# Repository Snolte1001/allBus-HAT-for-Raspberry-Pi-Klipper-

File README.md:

# allBus-HAT-for-Raspberry-Pi
I developed the expansion board to make all buses of the Raspberry Pi which are useful for the operation with Klipper easily accessible, to avoid wiring errors and to keep the construction as compact as possible.

Another requirement was to design the power management so that a proper startup and shutdown is possible, in addition there should be no standby power.  

## This HAT has no dependencies to Klipper, it can also be used for any other application without restrictions.

## **Power Funtions:**  
The HAT is supplied with 5V via screw terminals and can handle 3A current.  
a push button and an LED can be connected to the HAT on the port provided for this purpose.  
  
The button triggers a Mosfet circuit that supplies the Pi with power, the LED lights up as soon as the Pi starts.  
If the button is pressed again the LED starts blinking for 3 seconds, if pressed again during this time the Pi will initiate a proper shutdown and then reset the Mosfet, the Pi is now completely powerless.  
A long press of the button leads to a hard disconnect of the power supply.  

In addition, two GPIO(22,27) are led out which can be used, for example, to control a relay for the main power supply of a 3D printer (Attention: this would require a downstream circuit that switches the load with a transistor). 

For this Power ON/OFF function only one GPIO(4) is needed and does not limit the availability of the I2C bus because none of these pins is needed.  
Another GPIO(17) is used for the status LED. 

With a jumper you can choose if the Pi should boot automatically after applying the 5V power supply or if it should stay off.  

The basic idea of the ON/OFF circuit comes from this page:  
http://www.mosaic-industries.com/embedded-systems/microcontroller-projects/raspberry-pi/on-off-power-controller

## **Bus Features:**  
-CAN Bus on SPI0 (e.g. to connect the Pi internally with the MCU)   
-UART (e.g. to connect the Pi internally with the MCU)  
-SPI1 (e.g. for input shaper. Note: it still needs to be tested)  
-I2C (e.g. for input shaper)  

## **Installation:**  
1. preparation in boot/config.txt  
  coming soon
2. installation of the shutdown script  
  coming soon
  
## **Note for Klipper/MainsailOS/Fluidd users:**  
do not try to control the power control line (GPIO4) by software yourself ! This is blocked by the dtoverlay=gpio-poweroff, so it is also prevented that unintentionally a hard shutdown is triggered !

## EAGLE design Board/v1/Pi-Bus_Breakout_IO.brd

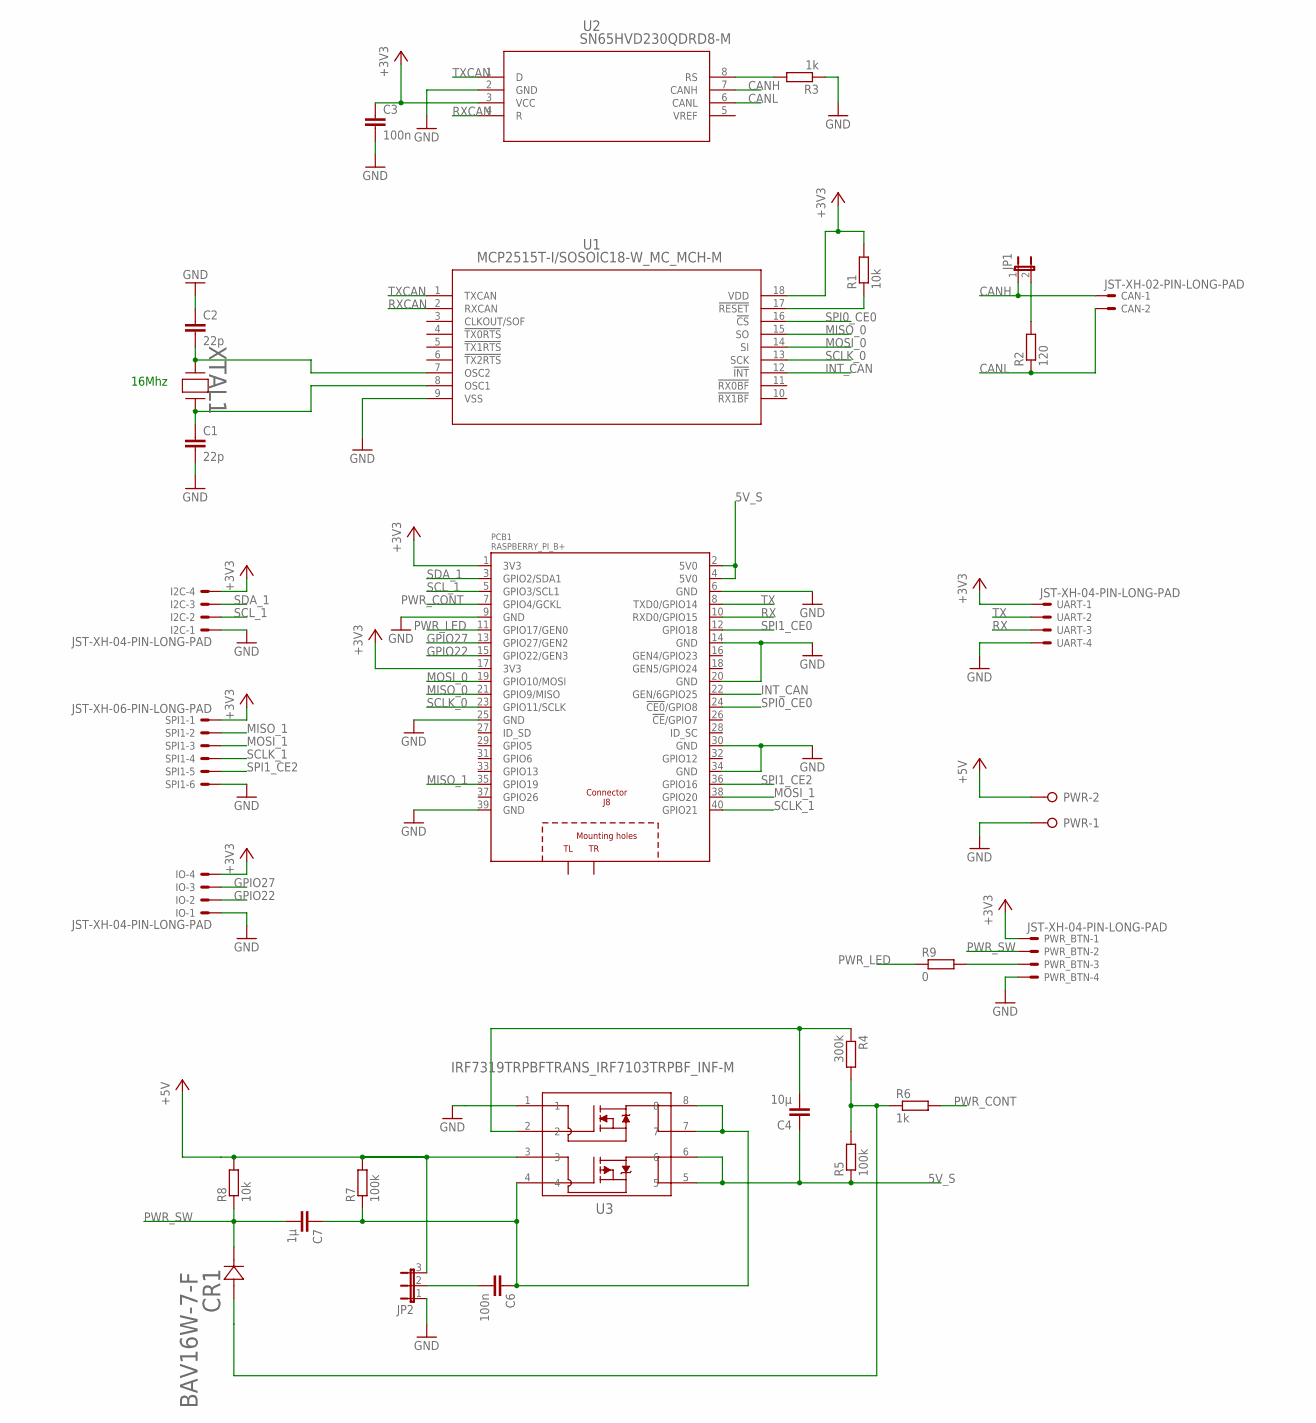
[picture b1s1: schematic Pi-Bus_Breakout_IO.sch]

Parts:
C1, C2: 22p; C0805
C3, C6: 100n; C0805
C4: 10µ; C0805
C7: 1µ; C0805
CAN: JST-XH-02-PIN-LONG-PAD; JST-XH-02-PACKAGE-LONG-PAD
CR1: BAV16W-7-F; SOD123_DIO
I2C: JST-XH-04-PIN-LONG-PAD; JST-XH-04-PACKAGE-LONG-PAD
IO: JST-XH-04-PIN-LONG-PAD; JST-XH-04-PACKAGE-LONG-PAD
JP1: JP1E; JP1
JP2: JP2E; JP2
PCB1: RASPBERRY_PI_B+
PWR: W237-02P; W237-132
PWR_BTN: JST-XH-04-PIN-LONG-PAD; JST-XH-04-PACKAGE-LONG-PAD
R1, R8: 10k; R0805
R2: 120; R0805
R3, R6: 1k; R0805
R4: 300k; R0805
R5, R7: 100k; R0805
R9: 0; R0805
SPI1: JST-XH-06-PIN-LONG-PAD; JST-XH-06-PACKAGE-LONG-PAD
U1: MCP2515T-I/SOSOIC18-W_MC_MCH-M; SOIC18-W_MC_MCH-M
U2: SN65HVD230QDRD8-M; D8-M
U3: IRF7319TRPBFTRANS_IRF7103TRPBF_INF-M; TRANS_IRF7103TRPBF_INF-M
UART: JST-XH-04-PIN-LONG-PAD; JST-XH-04-PACKAGE-LONG-PAD
XTAL1: 8Mhz; XTAL_8PF/ATF_EUR

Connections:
5V_S: C4.1, PCB1.2 (5V0), PCB1.4 (5V0), R5.1, U3.5, U3.6
+3V3: C3.1, I2C.4, IO.4, PCB1.1 (3V3), PCB1.17 (3V3), PWR_BTN.1, R1.2, SPI1.1, U1.18 (VDD), U2.3 (VCC), UART.1
+5V: JP2.3, PWR.2, R7.2, R8.2, U3.3
CANH: CAN.1, JP1.1, U2.7 (CANH)
CANL: CAN.2, R2.1, U2.6 (CANL)
GND: C1.2, C2.1, C3.2, I2C.1, IO.1, JP2.1, PCB1.6 (GND), PCB1.9 (GND), PCB1.14 (GND), PCB1.20 (GND), PCB1.25 (GND), PCB1.30 (GND), PCB1.34 (GND), PCB1.39 (GND), PWR.1, PWR_BTN.4, R3.1, SPI1.6, U1.9 (VSS), U2.2 (GND), U3.1, UART.4
GPIO22: IO.2, PCB1.15 (GPIO22/GEN3)
GPIO27: IO.3, PCB1.13 (GPIO27/GEN2)
INT_CAN: PCB1.22 (GEN/6GPIO25), U1.12 (!INT)
MISO_0: PCB1.21 (GPIO9/MISO), U1.15 (SO)
MISO_1: PCB1.35 (GPIO19), SPI1.2
MOSI_0: PCB1.19 (GPIO10/MOSI), U1.14 (SI)
MOSI_1: PCB1.38 (GPIO20), SPI1.3
unnamed: R1.1, U1.17 (!RESET)
unnamed: C1.1, U1.8 (OSC1), XTAL1.2
unnamed: C2.2, U1.7 (OSC2), XTAL1.1
unnamed: R3.2, U2.8 (RS)
unnamed: JP1.2, R2.2
unnamed: CR1.2, R4.2, R5.2, R6.1
unnamed: PWR_BTN.3, R9.2
unnamed: C4.2, R4.1, U3.2
unnamed: C6.2, JP2.2
unnamed: C6.1, C7.1, R7.1, U3.4, U3.7, U3.8
PWR_CONT: PCB1.7 (GPIO4/GCKL), R6.2
PWR_LED: PCB1.11 (GPIO17/GEN0), R9.1
PWR_SW: C7.2, CR1.1, PWR_BTN.2, R8.1
RX: PCB1.10 (RXD0/GPIO15), UART.3
RXCAN: U1.2 (RXCAN), U2.4 (R)
SCLK_0: PCB1.23 (GPIO11/SCLK), U1.13 (SCK)
SCLK_1: PCB1.40 (GPIO21), SPI1.4
SCL_1: I2C.2, PCB1.5 (GPIO3/SCL1)
SDA_1: I2C.3, PCB1.3 (GPIO2/SDA1)
SPI0_CE0: PCB1.24 (!CE0!/GPIO8), U1.16 (!CS)
SPI1_CE0: PCB1.12 (GPIO18)
SPI1_CE2: PCB1.36 (GPIO16), SPI1.5
TX: PCB1.8 (TXD0/GPIO14), UART.2
TXCAN: U1.1 (TXCAN), U2.1 (D)
VREF: U2.5 (VREF)

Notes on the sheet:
16Mhz

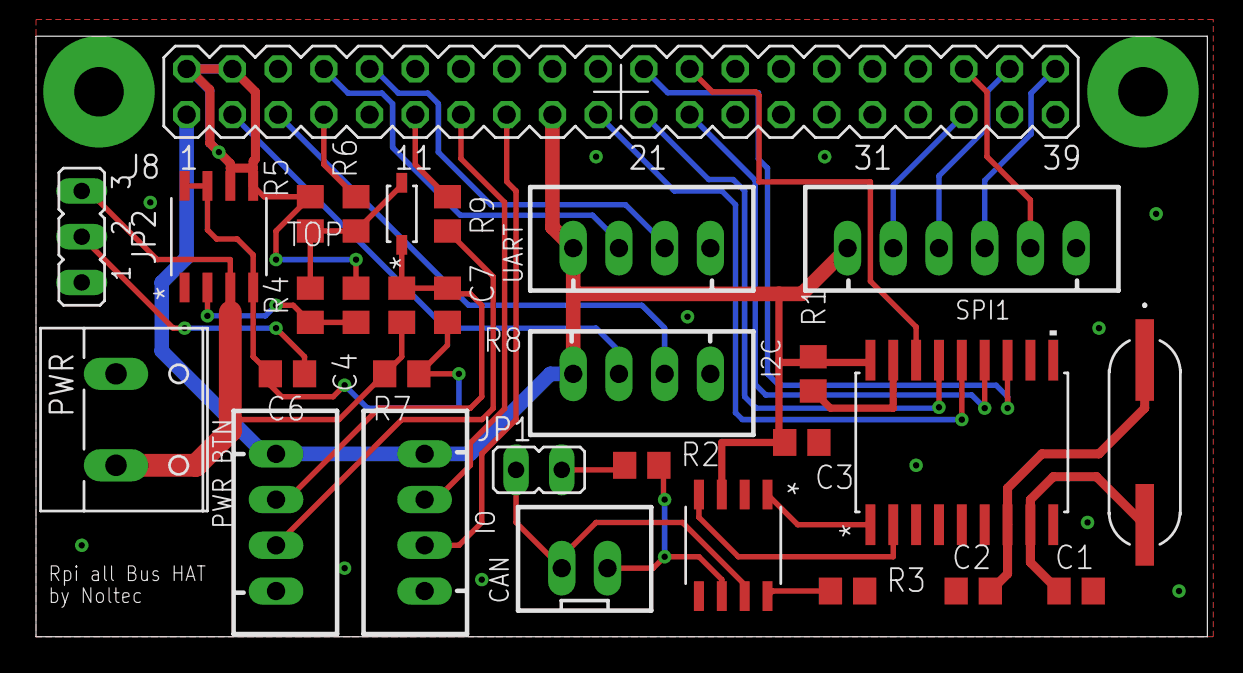
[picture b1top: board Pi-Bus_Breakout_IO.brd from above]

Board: 2 copper layers, 65.1 x 33.4 mm, 30 parts (0 on the bottom side), 36 nets.

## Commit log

2022-09-07 Create null
2022-09-07 Rename null to info
2022-09-07 Update and rename null to info

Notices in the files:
parts and their libraries:
COPYRIGHT: Copyright (C) 2022 Ultra Librarian. All rights reserved.
